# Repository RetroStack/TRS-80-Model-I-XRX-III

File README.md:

# TRS-80 Model 1 XRX-III Mod

This project faithfully reimplements the small brown mod board often seen attached to the keyboard of an TRS-80 Model 1. It corrects a software bug in earlier versions of the Level II ROMs, a bug later fixed in version 1.3. The design replicates the original mod's functionality using a 1-to-1 PCB design, including components, interfaces, and even traces.

Since this mod is no longer required for the latest ROM version, there's no need to create it. If you have an older computer, simply update the ROMs, and this mod becomes unnecessary. This repository serves more as a historical record and recreation of the board rather than for implementation.

For more details about this mod, visit: http://www.trs-80.org/xrx-modification/

The entire project is available under the MIT license.

## Project Details

### Latest Files

In the "Latest" folder, you'll find the most up-to-date design files, including:
- 3D views of the board
- The full schematics

### Implementation

This board has been implemented using KiCAD 7. The KiCAD project files are included in this repository.

### Schematic Details

The mod monitors when the cassette-interface-in flip-flop on the main board resets. Upon this event, it performs two actions:
1) it removes the clear from the 12-bit counter on the mod board, and
2) it sets a flip-flop to prevent the signal from the OpAmps from reaching the mainboard flip-flop for the cassette data-in.

The counter, utilizing a clock from the video circuitry, counts until 43.3ms have elapsed, after which it resets the mod flip-flop and reopens the cassette data-in port. This process helps to avoid noise being accidentally picked up by the software, which was listening too early (a bug in early system ROM versions).

The board employs two NOR gates for the flip-flop and uses the other two NOR gates to gate the CASSIN signal and then to invert its value (since the gating also inverts the data, restoring the original state of CASSIN). 

Another noteworthy aspect is the use of the two diodes and the pull-up resistor, configured to function like an AND gate. Opting for diodes and a resistor was likely a more cost-effective solution than adding another IC.

### RetroStack Libraries

To work with this KiCAD project, you'll need the RetroStack libraries for KiCAD. Please [follow this link](https://www.github.com/RetroStack/KiCAD-Libraries) to access and install these libraries.

## Main TRS-80 Model 1 Repository

For additional resources related to the TRS-80 Model 1, be sure to check out the [central page for the TRS-80 Model 1](https://www.github.com/RetroStack/TRS-80-Model-I) on [RetroStack](https://www.github.com/RetroStack).

## Support this Project

RetroStack is dedicated to learning about older computer systems and creating documentation and videos about them. We are also resurrecting older computer systems by reimplementing them and making replacement parts available for free. If you're interested in supporting this project, consider visiting our [Patreon page](https://www.patreon.com/RetroStack). Your support is greatly appreciated!

## License

This project is licensed under the MIT License - see the [LICENSE](LICENSE) file for details.

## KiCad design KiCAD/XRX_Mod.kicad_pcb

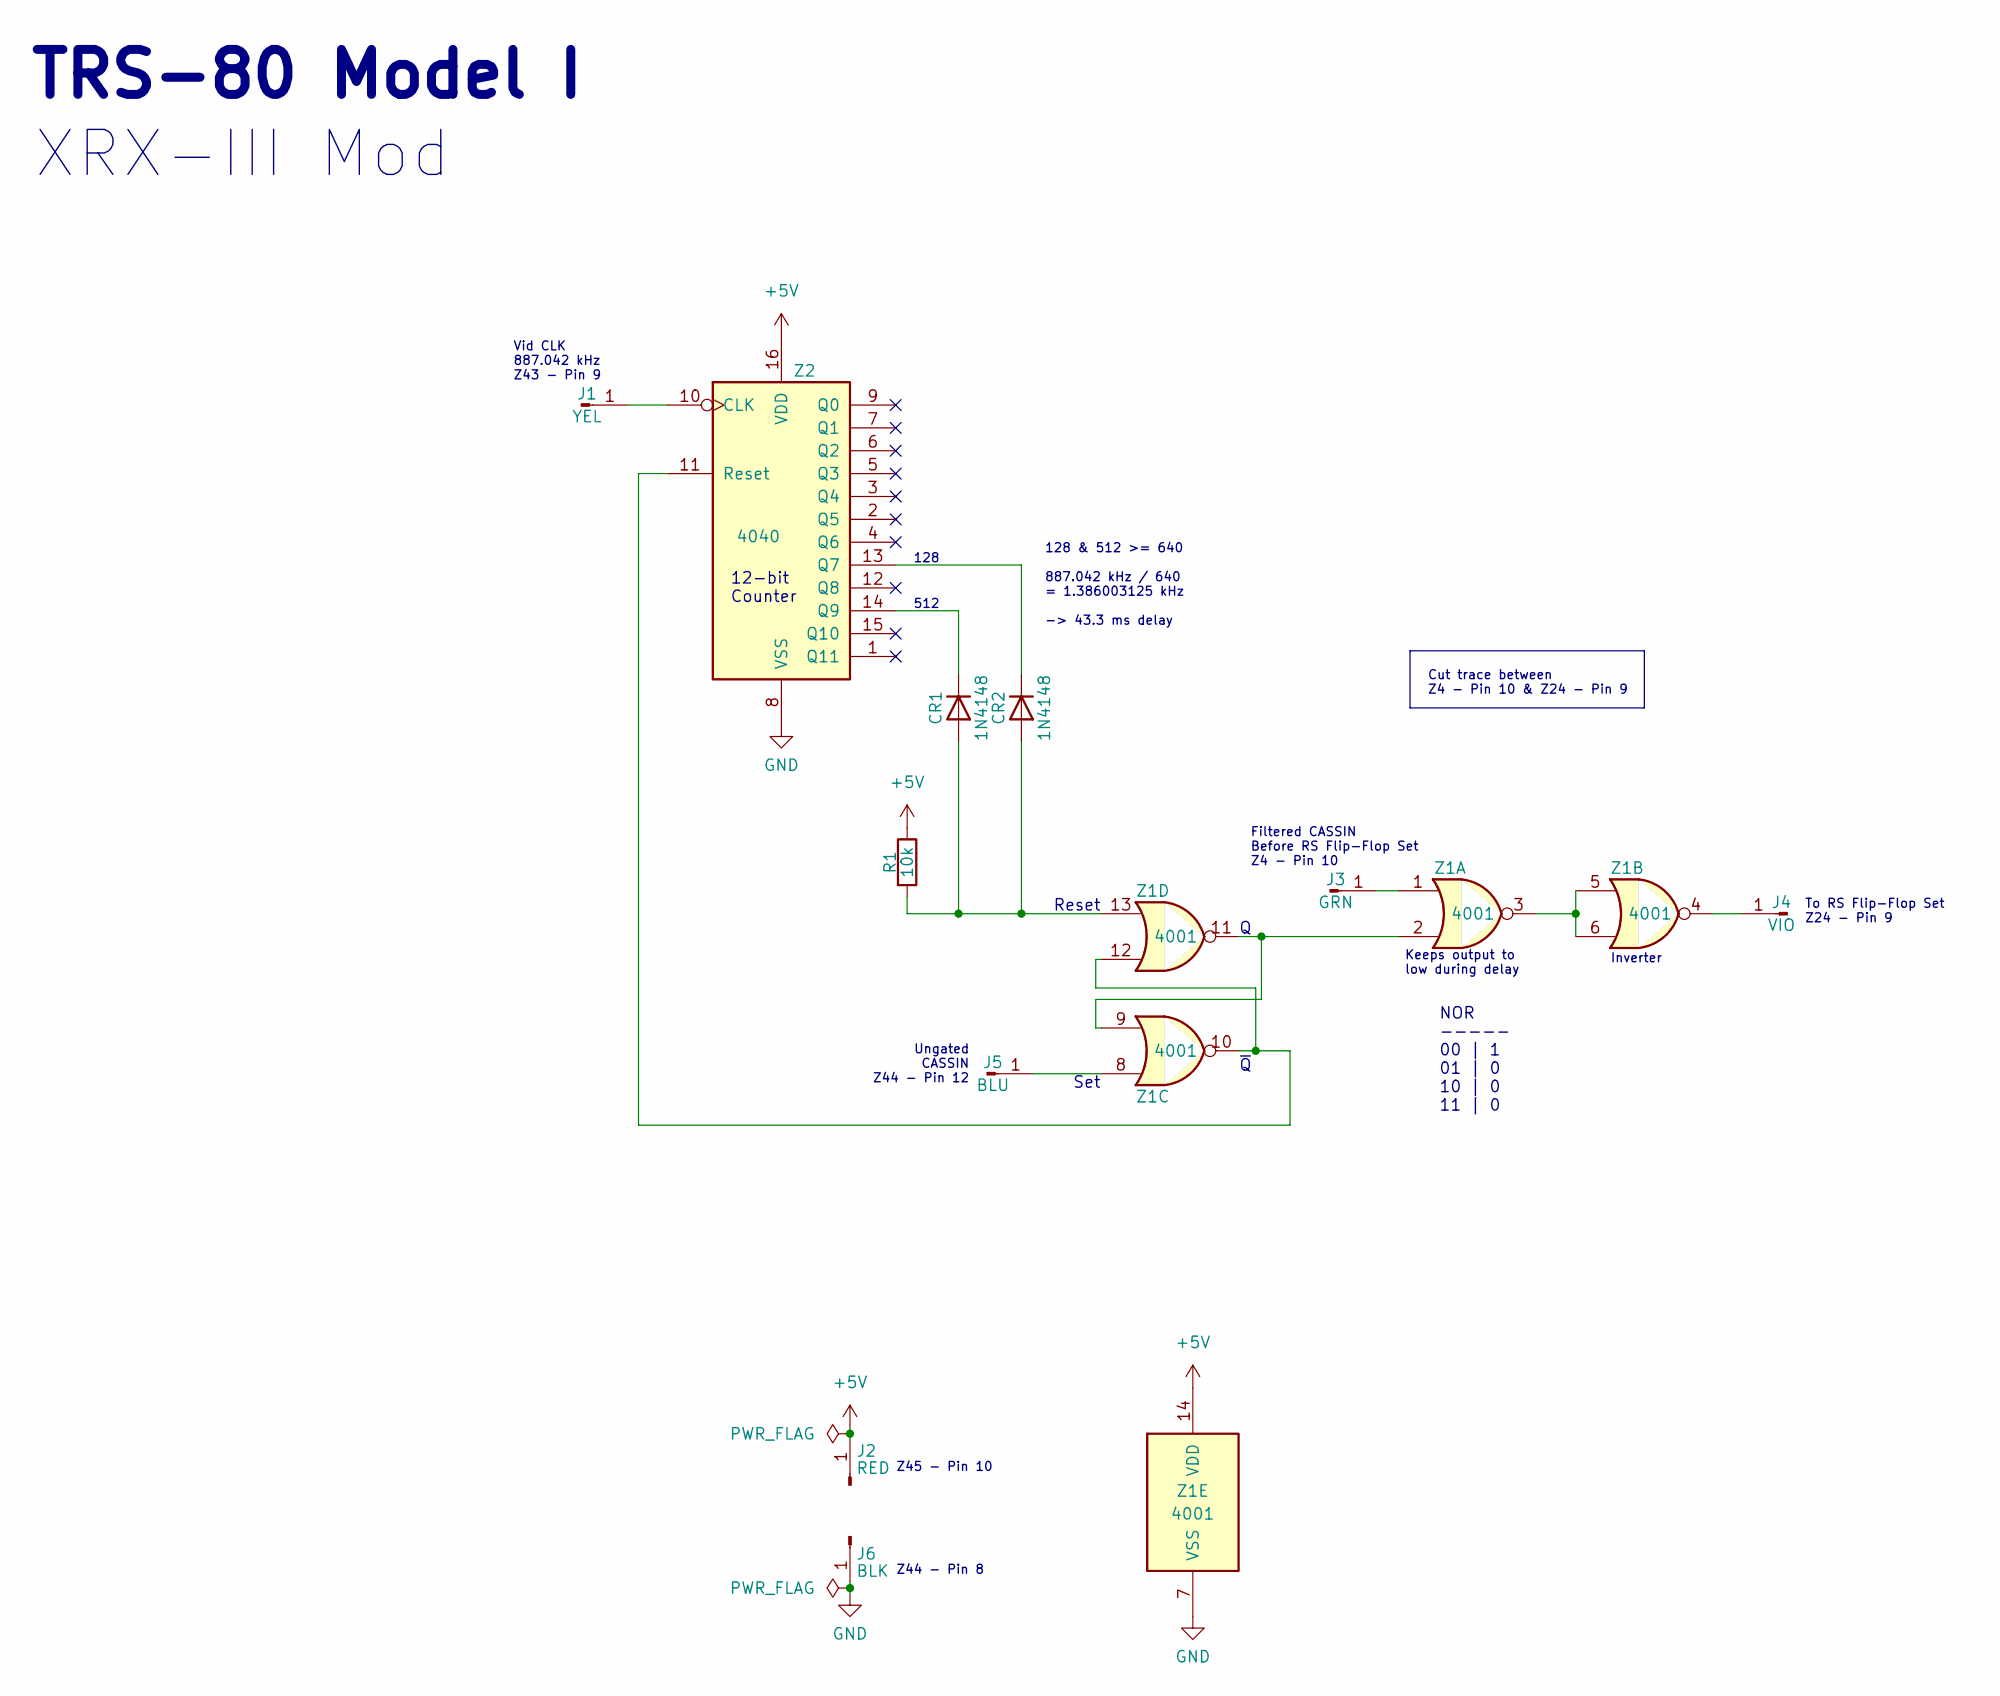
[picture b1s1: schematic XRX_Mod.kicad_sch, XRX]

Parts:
CR1, CR2: 1N4148; TRS80_Model_I_D
J1: YEL; PinHeader_1x01_P2.54mm_Vertical
J2: RED; PinHeader_1x01_P2.54mm_Vertical
J3: GRN; PinHeader_1x01_P2.54mm_Vertical
J4: VIO; PinHeader_1x01_P2.54mm_Vertical
J5: BLU; PinHeader_1x01_P2.54mm_Vertical
J6: BLK; PinHeader_1x01_P2.54mm_Vertical
R1: 10k; TRS80_Model_I_R_0.25W
Z1: 4001; TRS80_Model_I_DIP14
Z2: 4040; TRS80_Model_I_DIP16

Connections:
+5V: J2.1, R1.1, Z1.14 (VDD), Z2.16 (VDD)
GND: J6.1, Z1.7 (VSS), Z2.8 (VSS)
unnamed: CR1.2 (A), CR2.2 (A), R1.2, Z1.13
unnamed: CR1.1 (K), Z2.14 (Q9)
unnamed: CR2.1 (K), Z2.13 (Q7)
unnamed: J1.1, Z2.10 (CLK)
unnamed: J3.1, Z1.1
unnamed: J4.1, Z1.4
unnamed: J5.1, Z1.8
unnamed: Z1.3, Z1.5, Z1.6
unnamed: Z1.2, Z1.9, Z1.11
unnamed: Z1.10, Z1.12, Z2.11 (Reset)

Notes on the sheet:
Reset
TRS-80 Model I
Vid CLK 887.042 kHz Z43 - Pin 9
128
Cut trace between Z4 - Pin 10 & Z24 - Pin 9
To RS Flip-Flop Set Z24 - Pin 9
12-bit Counter
Filtered CASSIN Before RS Flip-Flop Set Z4 - Pin 10
Ungated CASSIN Z44 - Pin 12
Set
Keeps output to low during delay
Z44 - Pin 8
Inverter
NOR ----- 00 | 1 01 | 0 10 | 0 11 | 0
Z45 - Pin 10
128 & 512 >= 640 887.042 kHz / 640 = 1.386003125 kHz -> 43.3 ms delay
~{Q}
XRX-III Mod
512

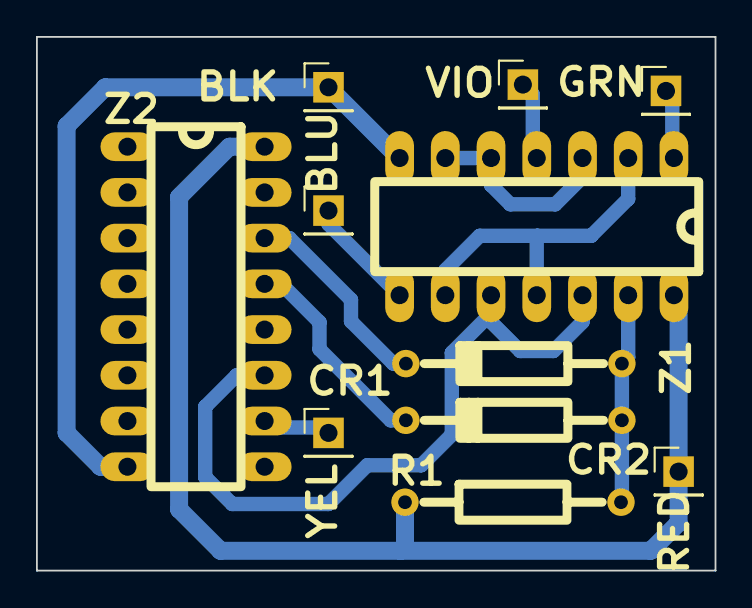
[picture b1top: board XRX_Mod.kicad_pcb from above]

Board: 2 copper layers, 37.7 x 29.7 mm, 11 parts (0 on the bottom side), 12 nets.

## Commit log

2024-01-05 Add overview
2024-01-14 Cleanup folders
2024-01-22 Update LICENSE
2024-08-23 Adding gerbers for JLCPCB only
